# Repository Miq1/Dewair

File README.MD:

# Important note
This project now is maintained on [Codeberg.org only](https://codeberg.org/Miq19/Dewair). The code here will be frozen at the current (Mar 30, 2025) state.

## Multi-purpose environment sensor device

DewAir was originally created to measure temperatures, humidity and dew point inside and outside a room and 
control a ventilator to dry out the room. 
It has been modified in the meantime to accomodate other functions as temperature alarm, remote weather sensor etc.

For this purpose it can be equipped with none, one or two DHT22 sensors, either plugged into the device or detached by a 3-wire cable.
Control over the vent is provided by a relais connected locally or over Modbus TCP to remotely switch a socket.

The device can be configured with a built-in HTML page or over Modbus TCP.
The latter also allows for data retrieval and maintenance. 
If more than one DewAir device is used, one can retrieve the sensor data from another over Modbus TCP, thus saving sensors. 

Power is supplied by USB or 5V, sensors and relais driver are powered internally.
Power consumption is below 90mA normally.

For schematics, PCB designs and 3D printable enclosures see the "Extras" folder.

### Installation

### Usage instructions

#### Start sequence
If powered on, the device will execute some initial steps until reaching normal function.
If it never was configured before (no valid configuration data found) it will immediately start Configuration mode (see next section). 
This is indicated by a slow triple blink pattern of the status LED.

Else there is a short (3s) fast blinking period. If you will press the button within this time, Configuration mode will be entered unconditionally.

Next configuration data is read, a WiFi connection is attempted with the given SSID and password. A fastly blinking LED will signal it.
Once a connection is established, both sensors are checked. If a sensor is found reacting the respective LED will turn on.

At this point the regular state is reached.

#### Configuration mode
In Configuration mode, the device will span its own WiFi network with a name of "DewAir-xxxxxx" and the given password in the source. This by default is "Maelstrom".

You will have to connect to that network to get access to the configuration. Please note that this WiFi is unencrypted and should not be kept online for too long.

Next you will want to open a browser to call the configuration HTML page with URL ``http://192.168.4.1/``. Note again that this is without TLS, so use ``http://``, not "https"!

The configuration page has several parts, described top to bottom below. Most input fields have minimum and maximum values that you may see if hovering over it with your mouse pointer.
The configuration may be invisible in parts at the first time, necessary detail input fields will be swapped in or out depending on your settings.

The most important part is the first, where you will have to enter a name of the new device and the WiFi credentials of your local WiFi for the device to connect to.
Below that you may give an OTA password in case you are planning to update the firmware over air.

The next is the "master switch". This is used to completely switch the logic and target switching on or off. With it you may temporarily disable the device's activities for re-configuration etc. It is advisable to leave it OFF for the first time you are configuring it to be able to cross-check your configurations before going live.

Next comes the "fallback policy". This is to set a default target state in case the sensors or logic will fail at some time.
If set to ON, a failure will drive the device to unconditionally switch the target to ON.
The device logic may be resumed as soon as the causing failure is gone again.
The advisable state of the fallback switch is totally up to you and your application. A frost protector f.i. may better be switched ON, while a motorized door may have to be OFF instead.

Finally the "hysteresis" can be adjusted. Hysteresis means defining a number of necessary, consecutive measurements, whose results have lead to the same logic decision to switch the target.
Hysteresis consists of two components: a number of measurements in a row necessary and the time between measuring actions.
To give an example: a number of 5 measurements and a time of 20s will require the logic to decide the same for all 5 checks in 100s.
Only if all 5 resulted in either all ON or all OFF decisions, the switch finally will be done, if applicable.
The intended result is a less "nervous", steady switching behaviour that does not react on single dropout measurements.

The target definition is required should you want to physically switch something on or off based on the sensor data.
If the device is used as a temp/humidity sensor only, the target may be left unconfigured.
A target may be one of three variants: "ignore", if not relevant as described before, "connected", if the device's relay port is used for it, or "Modbus" for a remote "[Smartdose](https://github.com/eModbus/Smartdose)" socket addressed via Modbus.
To use the latter, the TCP IP address, Modbus port number and Modbus server ID for it are required.

Sensor configuration is quite similar to that of the target device.
The "ignore" option leaves the respective sensor slot unregarded. At the same time the combo conditions (see below) will vanish, since 
these only make sense with two sensors present.

The data for a remote, Modbus-connected sensor are the same as before for the target, with one addition: sensor slot.
A remote sensor must reside in another DewAir device to be addressed. As there are two sensor slots, you will need to name the one you are referring to.

A typical application for a remote sensor is to have just one sensor outside the building and all other devices inside it referring to the values of that one sensor.

The conditions section allows to set the conditions the respective sensor must detect to enable the target to be switched on.
Temperature, humidity or dew point can be addressed separately, the results of the evaluations are combined by a logical "and".
If you f.i. want to switch the target on a temperature higher than 10&#176;C and do not care about humidity or dew point, you will want to click on "above" in the temperature line and enter a value of 10 in the data input field. 
Both humidity and dew point options need to be set to "ignore".

Conditions set for a device that later was set to "ignore" as a device will remain unconsidered.

Likewise the combination conditions can be set. There always is a difference of the respective measurement of sensors S0 and S1 taken as the criteria for the conditions.
The settings for the conditions are identical to those with the individual sensor conditions.

#### LED decoding
There are four LEDs on the device in this order: status, S0, S1 and target. 
I recommend to use a different LED color for the status LED for better recognition.

##### Status LED
It will signal the general state the device is in. The start sequence is described above.

In manual mode the status LED will be steadily on, the target LED will show the switch state of the target.

If the target is supposed to be off as result of the evaluation of the conditions, the status LED will display a slow single blinking pattern.

Else, if the target is to be on, the status LED will send a triple blink with a pause in between.

Whenever a measurement is initiated, the status LED will turn on and off after it.

##### Sensor LEDs S0/S1
The respective sensor LED will turn on, if the sensor was configured and a measurement was successful.
A sensor not configured will be displayed by its LED being constantly off.

If a sensor was not responding, the LED will start blinking very quickly. It will resume the regular pattern as soon as the sensor responded again.

##### Target LED
For remote (Modbus) targets, the LED will behave like the sensor leds do: steady on for responding target, quick blinking when the target did not react.

A local target has no such diagnosis, but its state (on or off) will be shown by the LED being lit for ON and dark for OFF state.

#### Button functions
Besides the special interaction during startup (see above for the start sequence) the push button has three different applications.

- Quick press<br/>will start a check of the sensors and target, if any, like is done repeatedly while the device is running.
- Long press<br/>starts manual mode. In it, the sensors are ignored and further short presses will switch the target on and off in turns.
  Another long press will end manual mode and return to automatic control.
- Double click<br/>the conditions for sensor S0, S1 and the combination conditions are checked. If the respective conditions are met,
  the respective sensor LED will light. The target LED stands for the combination conditions.

### Modbus register map

| Register address | type | Contents | Write? | Remarks |
| ----------------:| ---- | -------- |:------:| ------- |
| 1       | uint   | Master switch   | YES | Disable switching logic |
| 2, 3    | float  | S0 temperature  |     | DHT22 sensor 0 |
| 4, 5    | float  | S0 humidity     |     |                |
| 6, 7    | float  | S0 dew point    |     |                |
| 8, 9    | float  | S1 temperature  |     | DHT22 sensor 1 |
| 10, 11  | float  | S1 humidity     |     |                |
| 12, 13  | float  | S1 dew point    |     |                |
| 14      | uint   | Switch state    |     |  Current target switch state |
| 15      | uint   | Restart count   |     |  Number of reboots since last init |
| 16      | uint   | Run time in minutes | |  Minutes since last reboot. Will halt at 65535. |
| 17      | uint   | S0 health       |     |  Each '1' bit stands for a successful read |
| 18      | uint   | S1 health       |     |                |
| 19      | uint   | Target health   |     |                |
| 20      | uint   | Measuring interval in seconds | YES | Must be 10 &le; n &le; 3600 |
| 21      | uint   | Hysteresis steps | YES | Must be 1 &le; n &le; 16 |
| 22      | uint   | S0 type          | YES | 0: none<br/> 1: connected locally<br/> 2: ModbusTCP source<br/> 3: reserved |
| 23, 24  | byte[4] | S0 Modbus IP address | YES | MSB first |
| 25      | uint   | S0 Modbus port number | YES | Must be &ge; 1 |
| 26      | byte[2] | MSB: S0 Modbus server ID<br/>LSB: slot number | YES | 1 &le; MSB &le; 247<br/> LSB: 0 or 1 |
| 27      | special | S0 temperature condition:<br/> bits 14,15: condition type<br/> bits 0..13: compare value | YES | *type:*<br/> 0: disregard<br/> 1: less than value<br/> 2: greater than value<br/>3: reserved<br/>*value:*<br/> ``float val = (int(value) - 2048) / 10.0;``|
| 28      | special | S0 humidity condition/value (as above) | YES | see above |
| 29      | special | S0 dew point condition/value (as above) | YES | see above |
| 30      | uint   | S1 type          | YES | see S0 type |
| 31, 32  | byte[4] | S1 Modbus IP address | YES | MSB first |
| 33      | uint   | S1 Modbus port number | YES | Must be &ge; 1 |
| 34      | byte[2] | MSB: S1 Modbus server ID<br/>LSB: slot number | YES | 1 &le; MSB &le; 247<br/> LSB: 0 or 1 |
| 35      | special | S1 temperature condition:<br/> see S0 | YES | see S0 |
| 36      | special | S1 humidity condition/value (as above) | YES | see above |
| 37      | special | S1 dew point condition/value (as above) | YES | see above |
| 38      | uint   | Target type           | YES | 0: none<br/> 1: connected locally<br/> 2: Modbus TCP target<br/> 3: reserved |
| 39, 40  | byte[4] | Target Modbus IP address | YES | MSB first |
| 41      | uint   | Target Modbus port number | YES | Must be &ge; 1 |
| 42      | uint   | Target Modbus server ID   | YES | **MSB only!**<br/> Must be 1 &le; SID &le; 247 |
| 43      | special | (S0 temperature - S1 temperature) condition type and value | YES | see S0 temperature condition and type above |
| 44      | special | (S0 humidity - S1 humidity) condition type and value | YES | see above |
| 45      | special | (S0 dew point - S1 dew point) condition type and value | YES | see above |
| 46      | uint    | nibble 0: number of combo conditions met<br/>nibble 1: number of S1 conditions met<br/>nibble 2: number of S0 conditions met<br/>nibble 3: unused |     | debug info |
| 47      | uint    | Fallback switch setting | YES | 0: OFF<br/>else: ON |
| 48      | uint    | Number of history slots |     | 1440 minutes a day / slots = minutes within a slot for values to be averaged |
| 49      | uint    | Start address of first history slot entry |     | see section below! |
| 50      | uint    | Currently written history data slot |     | see below! |
| 51 .. 63 |    | *reserved* | YES | future extension space |
| 64      | uint    | Number of event slots |    | if 0: no events available |
| 65 ..   | special | Logged events (number see register 64) |     | bits 11 .. 15: Event code<br/>bits 6 .. 10: day/hour<br/>bits 0 .. 5: month/minute |

#### History entries
For each history slot, temperatures and humidities of both sensors (if available) are averaged over the values within that slot.
The slots are ordered from 0=00:00 to (history slots - 1)=last before midnight.
Times as are related to slots can be calculated as follows:
- 1440 / history slots = minutes per slot. The default 120 slots translate to 12 minutes per slot.
- A given slot number needs to be multiplied by the minutes per slot, then has to be separated into hour and minute.
  Example: slot 67 is 67 * 12 = 804 minutes since midnight. Divided by 60 this is 13 hours. The remainder are 24 minutes.
  Hence the slot 67 is starting at 13:24 (1:24pm).
To fit into an ``uint16_t`` register, values are encoded:
- temperature: (avg(temp) + 100) * 10. ``1256`` will mean 25.6 degrees.
- humidity: avg(hum) * 10. ``489`` stands for 48.9% RH.
Additionally the percentage of the target being on is collected.
All time ON withing the slot is 100%, never ON is 0%.

| Register address | type | Contents | Write? | Remarks |
| ----------------:| ---- | -------- |:------:| ------- |
| History offset..history offset + history slots - 1 | uint   | Sensor 0 temperature history values |  | encoded as described above |
| like the above, History slots added | uint   | Sensor 0 humidity history values |  | encoded as described above |
| like line 1, 2 * History slots added | uint   | Sensor 1 temperature history values |  | encoded as described above |
| like line 1, 3 * History slots added | uint   | Sensor 1 humidity history values |  | encoded as described above |
| like line 1, 4 * History slots added | uint   | Target switch ON percentage |  | see section above |

### Applications

#### Dew point ventilation

#### Frost protection

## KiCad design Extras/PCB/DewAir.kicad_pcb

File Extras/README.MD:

# Extras
This folder contains additional components and materials I developed for my DewAir devices - namely, the dew point ventilation controller and the frost protection device.

- Enclosure contains FreeCAD 3D designs and STL files for a small and a large box. The small one is powered by USB or 5V and needs a WiFi socket as target device, the larger box has all inside to run autonomously when connected to a wall power outlet.
- Fan Mount has 3D FreeCAD designs and STLs as well for attaching a 100mm standard tube ventilator or a 100mm air gauge to a window pane. I replaced the glass panes by acrylic glass and cut a hole in in to fit the mount. A drilling/cutting template can be 3D printed as well.
- PCB holds all KiCAD and Gerber files necessary to have the PCB manufactured.
- ``DewAir.cpp`` is a Linux command line tool to configure and control any DewAir device. It requires the Linux port of the [eModbus](https://github.com/eModbus/eModbus) library to be built - found there in the [examples/Linux](https://github.com/eModbus/eModbus/tree/master/examples/Linux) directory.
See below for build instructions etc.

### DewAir Linux tool
All interaction with the device is done by Modbus TCP. 
You of course may use other Modbus TCP clients to achieve the same, but you will need to closely inspect the Modbus register list for it.
The ``DewAir`` tool has all the definitions built in and lets you use plain text words to interact with the device.

#### Build and Install
As a prerequisite you will need to build the Linux eModbus library as mentioned in the first section.
With that available you can compile the program by
```
g++ DewAir.cpp -Wextra -DLOG_LEVEL=3 -MMD -leModbus -pthread -lexplain -o DewAir
```
#### Usage
Running ``DewAir`` without any parameter will display the supported options:
```
micha@LinuxBox:~$ DewAir 
At least one argument needed!

Usage: DewAir host[:port[:serverID]]] [cmd [cmd_parms]]
  cmd: INFO | ON | OFF | EVERY | EVENTS | INTERVAL | HYSTERESIS | TARGET | SENSOR | CONDITION | FALLBACK | REBOOT | ERRORS | HISTORY
  ON|OFF
  FALLBACK ON|OFF
  EVERY <seconds>
  EVENTS
  ERRORS
  HISTORY
  INTERVAL <seconds>
  HYSTERESIS <steps>
  TARGET NONE|LOCAL|<host[:port[:serverID]]]>
  SENSOR <0|1> NONE|LOCAL|<<host[:port[:serverID]]]> <0|1>>
  CONDITION <SENSOR <0|1>>|DIFF TEMP|HUM|DEW IGNORE|<BELOW|ABOVE <value>>
  REBOOT
```
``DewAir`` needs a device as first parameter in any case.
This can be the DNS name the device has been assigned, or a detailed address consisting of an IP address, a port number and a Modbus server ID, separated by colons (':').
If omitted, the server ID defaults to 1, the port number is 502 by default.

After the address of the device a command is expected. If none was given, ``INFO`` is taken as a default.

#### INFO
With ``INFO`` the current data is requested from the device. Sample output:
```
micha@LinuxBox:~$ DewAir anbau 
Using 192.168.178.30:502:1
Master switch ON
Fallback: switch ON
Sensor 0:  12.1°C   56.0%    3.6°C  - FFFF
Sensor 1:   6.4°C   45.8%   -4.4°C  - FFFF
Target is OFF - FFFF 192.168.178.40:502:1
Measuring every 30 seconds, hysteresis steps: 4
86 restarts, run time since last restart 24:48
40 event slots
120 history slots starting at 400, current is 83
Switch conditions (all must be true): 
 + S0 temperature below   5.0°C
Condition state: 0233
```
You see how the DNS name ``anbau`` is translated internally to a full address.
The device is active (master is ON), on failures it will switch the target to ON.
Both sensors are connected locally and are performing well (``FFFF`` tells us the last 16 sensor requests were successful).
The target device is a Modbus-controlled remote socket, it is currently OFF and communication was okay (``FFFF`` again).
Sensors are requested every 30 seconds and 4 consecutive identical evaluations of the conditions set will trigger a switching action.
The device was restarted 86 times and is running more than a day now after the last restart.
It does register the last 40 events (see below) and the data history has 120 time slices over a day. Modbus register 400 holds the first history value.
The device is set to switch the target as soon as sensor 0 will report a temperature below 5 degrees. Current temperature is above that, so the state is not ``0333`` as it would be with all conditions met.

#### ON/OFF
This will activate or deactivate the device. The 'Master switch' is turned ON or OFF.
If set to OFF, the device will work as normal, but never will touch the target's state.

#### FALLBACK
If sensors have malfunctions or are not responding, there is no reliable evaluation of the switch conditions possible any more.
``FALLBACK`` defines the target state that will be set in such situations.
F.i. a frost protection device may set to fall back to ON state to prevent freezing - for the cost of unnecessary energy wasted.

#### EVERY
``EVERY`` will request and print out the sensor and target state values in the intervals given as additional seconds parameter.
Note that this value must be 60 or higher to prevent the device being flooded with requests.
The output is a comma separated list for easy processing in a spreadsheet program. To have an output readable on the terminal you should pipe it through a ``tr`` like in
```
micha@LinuxBox:~$ DewAir anbau every 60 | tr ';' '\t'
Using 192.168.178.30:502:1
Time    S0                      S1                      Diff                    target
        temp    hum     dew     temp    hum     dew     temp    hum     dew
17:25   12.2    53.0    2.9     5.6     47.2    -4.8    6.6     5.8     7.7     0
```
Output can be stopped by ``Ctrl C`` only.

#### EVENTS
Important things happening will be recorded on the device in the ``EVENTS`` list. It looks like
```
micha@LinuxBox:~$ DewAir anbau events
Using 192.168.178.30:502:1
40 event slots found.
target off           18:06
target off           20:05
target off           20:06
target off           22:05
target off           22:06
date change     01.03.
target off           00:05
target off           00:06
target off           01:09
target off           02:05
target off           04:05
target on            04:49
target off           04:54
target on            05:28
...
```
(Note: in this example the target itself is programmed to turn on every two hours, so as soon as the DewAir device notices the target being ON, it will switch it OFF again).

#### ERRORS
Similar to the events, Modbus errors are recorded on the device.
With the ``ERRORS`` command you may retrieve what was stored:
```
micha@LinuxBox:~$ DewAir anbau errors
Using 192.168.178.30:502:1
Back : ERR  Count
    0:  00    229 - Success
    1:  E0      1 - Timeout
    2:  00    410 - Success
    3:  EA      1 - IP connection failed
    4:  00    937 - Success
```
Only if the Modbus state has changed a new entry is made. Else only the number of occurrences of the same state will be counted.
Note that the most recent state is shown on top, the lower, the older the stes are.

#### HISTORY
All sensor data and target states are collected for 24h. Values older will be replaced by current values as time proceeds.
The data is averaged over time slots. A slot is 12 minutes wide in the default code.
Hence you will have 120 slots per 24h that can be retrieved in a single Modbus request.
There are 120 such values for sensor 0 temperature, humidity, sensor 1 temperature and humidity and the target state value. 
A complete history data set will have 600 values, each in a Modbus register.
Floating point sensor values are encoded to fit into the 16 bits of a Modbus register.
The coding scheme is described on the main page - see section 'History' there.

The ``HISTORY`` command will do all 5 requests and the decoding in one step and outputs the data as a comma-separated list to be processed in a spreadsheet program.
It is advisable to catch the output in a file and open it in a spreadsheet:
```
micha@LinuxBox:~$ DewAir anbau history > anbau.csv
```
With a bit of massaging in the spreadsheet you can quickly get some nice diagrams:

A sixth column is added to the output that is almost empty. The exception is a ``#`` sign in that row where the next slot will be written.
So right of that line is data from the previous day, left of it the data for the current day up to now.

In the diagram above I used a simple formula (``=IF($H3=" ";$G2;100)``) to have a line jump up at the current slot. It will take a zero as start value and always replicate the value of the line above - except if the neighbouring cell has something other than a blank in it; then the value will set to 100.

#### REBOOT
A mechanism has been integrated to remotely restart a DewAir device. 
It makes use of the user-definable Modbus function code 0x44.
``REBOOT`` has to be sent twice within 60 seconds to have an effect. 
This is meant as a basic security mechanism. 
The first ``REBOOT`` will be answered by ``armed.``, the second, if received within the 60s period, will print out ``rebooting.``.
If the second commend is late or not given at all, the ``armed`` state will be reset on the device.

#### INTERVAL ``<seconds>`` and HYSTERESIS ``<turns>``
These two commands will modify the reaction speed of the device on changing sensor data.
Data is sampled every ``INTERVAL`` seconds. Note that the seconds parameter can not be lower than 20 to not overload the device.

``HYSTERESIS`` sets a number of sampling periods where the sampled values are fulfilling the switching conditions without exception.
If that happens, a switch is executed.

F.i. a combination of 30 seconds and a hysteresis of 6 will require the switch conditions to last at least 3 minutes to trigger a switch.
Higher values will lead to a slower, smoother switching behaviour, whereas short intervals or less hysteresis periods will let the device react more quickly.
It depends from your application which may be the adequate setting.

#### TARGET
The ``TARGET`` command lets you define if there is a switching target at all and what type it is.

A ``TARGET NONE`` will disable any switching actions, while sensor data still is collected.
This may be useful if you are using a DewAir device as a remote temperature/humidity platform to read these data and make it available to other devices.
Please see the ``SENSOR`` explanations in the section below.

``TARGET LOCAL`` enables the device to use the internal relay/SSR logic as a target. 
A stand-alone DewAir device may switch a built-in socket this way.

Finally ``TARGET <Modbus address>`` allows for remote target devices that can be switched by a Modbus request.
At this time only the [Smartdose](https://github.com/eModbus/Smartdose) type of devices is supported. 
Other WiFi sockets will need a different command or even different protocol that would have to be integrated first.
Contributions are always welcome... :wink:

The Modbus address needs to be given as described above for the first parameter of the DewAir application itself: either a DNS name or a set of IP address, port and server ID, joined by colons ':'.

#### SENSOR
Each of the two attachable sensors may be non-existent, plugged in locally into the device or other DewAir devices in the same local network.

``SENSOR`` always needs a sensor number first, that can be ``0`` for the first or ``1`` for the second DHT22 sensor.

After that we can have ``NONE`` to disable the sensor slot, ``LOCAL`` for sensors connected by wire to the device, or a Modbus address again to connect to another DewAir device.

The Modbus address has to follow the very same rules as described above for the DewAir application or the ``TARGET`` parameter.
It requires one more parameter after it, though: the sensor slot on the remote device.
This slot addresses the two sensors on that device the same way as we are doing here: ``0`` is the first, ``1`` the second sensor.

Instead of collecting the data locally, a remote sensor will be requested by Modbus. 
Note that due to the communication delays and collecting interval on the remote device the data gathered remotely may not exactly be measured at the same time the request was sent, but will be delayed for some seconds.

#### CONDITION
If and when a target gets switched is depending from the conditions you have defined in regards to the sensor data.
The ``CONDITION`` command lets you set these conditions at will.

First you will have to tell what conditions you are going to set:
- ``SENSOR 0`` or ``SENSOR 1`` will select the respective sensor
- ``DIFF`` instead will target on conditions for both sensors combined. Note that this is not possible if one or both sensors are set to ``NONE``!

The next parameter selects the data type you are using for the condition - ``TEMP`` for temperature, ``HUM`` for humidity or ``DEW`` for the dew point temperature evaluated internally.

Last is the condition proper:
- ``IGNORE`` disables it to not be regarded any more
- ``BELOW <value>`` will result ``TRUE`` if the selected data is lower than the given ``<value>``
- opposite, ``ABOVE <value>`` will be ``TRUE`` if the data is higher than ``<value>``

Example:
```
DewAir condition sensor 0 temp below 5
```
will require the first sensor's temperature to be lower than 5 degrees Celsius to be evaluated to ``TRUE``.

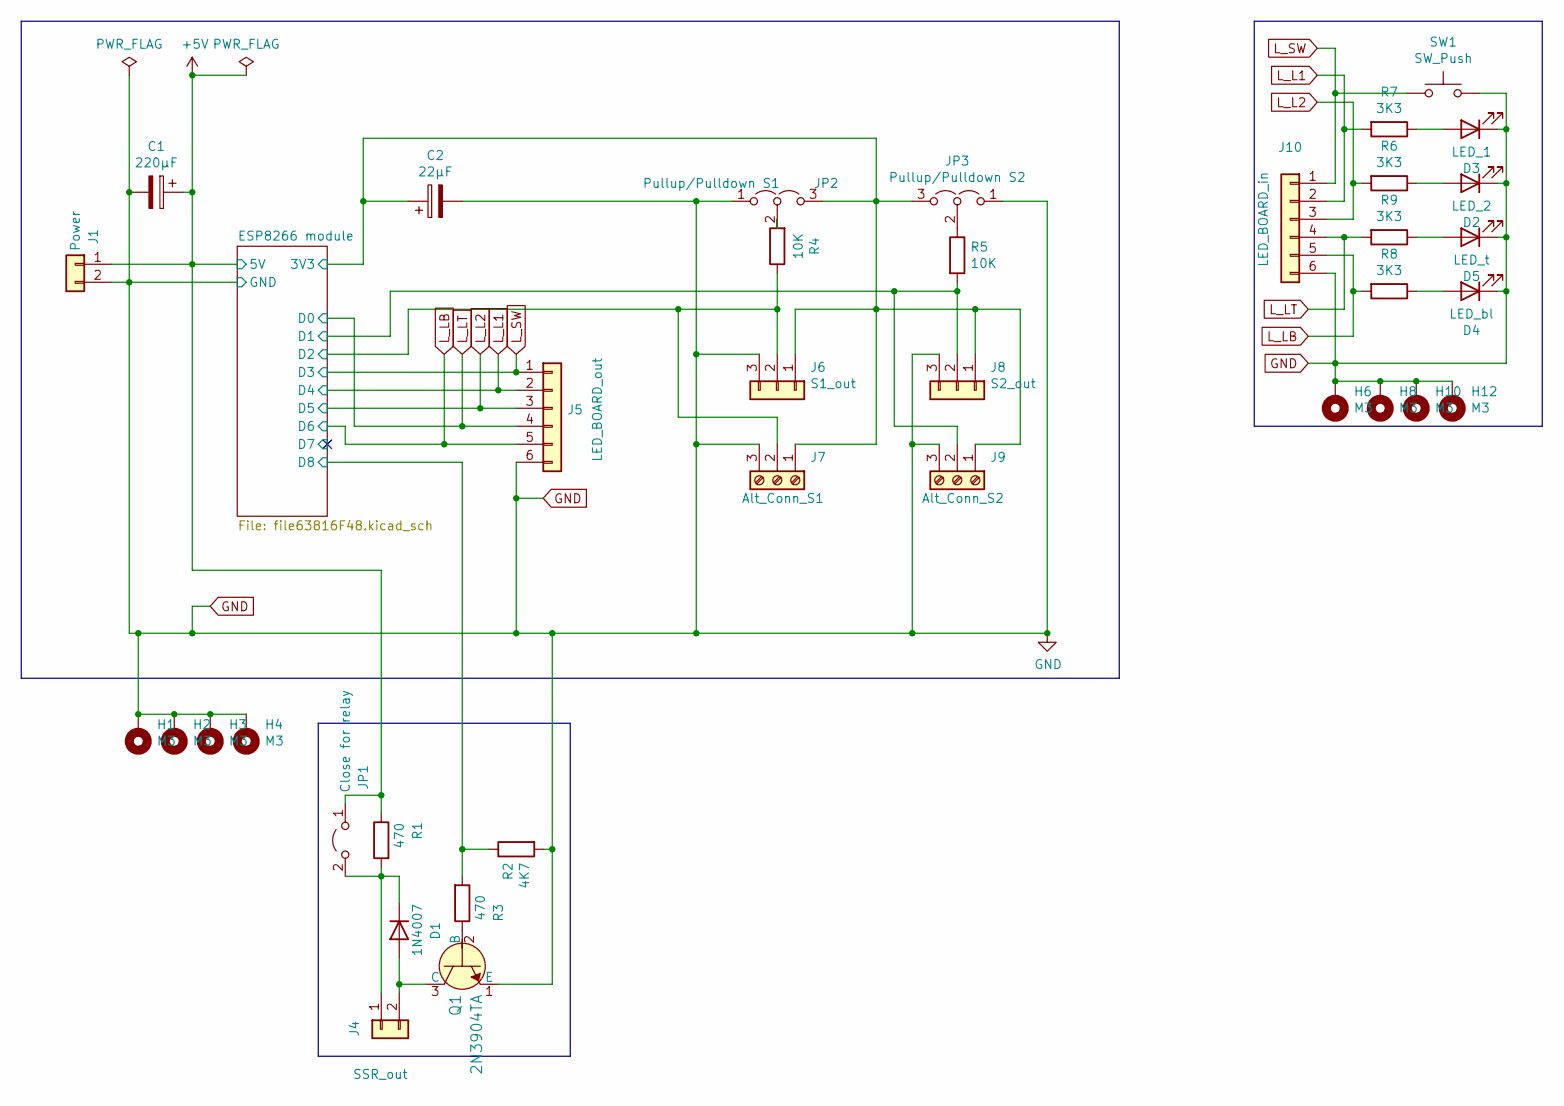
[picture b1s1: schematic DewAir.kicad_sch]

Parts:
C1: 220µF; CP_Radial_D5.0mm_P2.00mm
C2: 22µF; CP_Radial_D4.0mm_P2.00mm
D1: 1N4007; D_A-405_P7.62mm_Horizontal
D2: LED_2; LED_D3.0mm
D3: LED_1; LED_D3.0mm
D4: LED_bl; LED_D3.0mm
D5: LED_t; LED_D3.0mm
H1, H2, H3, H4, H6, H8, H10, H12: M3; MountingHole_3.2mm_M3_DIN965_Pad
J1: Power; TerminalBlock_bornier-2_P5.08mm
J4: SSR_out; TerminalBlock_bornier-2_P5.08mm
J5: LED_BOARD_out; Pin_Header_Straight_1x06_Pitch2.54mm
J6: S1_out; JST_XH_B03B-XH-A_03x2.50mm_Straight
J7: Alt_Conn_S1; TerminalBlock_bornier-3_P5.08mm
J8: S2_out; JST_XH_B03B-XH-A_03x2.50mm_Straight
J9: Alt_Conn_S2; TerminalBlock_bornier-3_P5.08mm
J10: LED_BOARD_in; Pin_Header_Straight_1x06_Pitch2.54mm
JP1: Close for relay; Pin_Header_Straight_1x02_Pitch2.54mm
JP2: Pullup/Pulldown S1; Pin_Header_Straight_1x03_Pitch2.54mm
JP3: Pullup/Pulldown S2; Pin_Header_Straight_1x03_Pitch2.54mm
Q1: 2N3904TA; TO-92_Inline; MPN 2N3904TA; Digi-Key_PN 2N3904TAFSCT-ND
R1, R3: 470; R_Axial_DIN0207_L6.3mm_D2.5mm_P7.62mm_Horizontal
R2: 4K7; R_Axial_DIN0207_L6.3mm_D2.5mm_P7.62mm_Horizontal
R4, R5: 10K; R_Axial_DIN0207_L6.3mm_D2.5mm_P7.62mm_Horizontal
R6, R7, R8, R9: 3K3; R_Axial_DIN0207_L6.3mm_D2.5mm_P7.62mm_Horizontal
SW1: SW_Push; SW_PUSH_6mm_h9.5mm

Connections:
+5V: C1.1, J1.1, JP1.1 (A), R1.1; also elsewhere on the board
/ESP8266 module/3V3: C2.1, J6.1, J7.1, J8.1, J9.1, JP2.3 (B), JP3.3 (B); also elsewhere on the board
/ESP8266 module/D1: J8.2, J9.2, R5.2; also elsewhere on the board
/ESP8266 module/D2: J6.2, J7.2, R4.1; also elsewhere on the board
/ESP8266 module/D8: R2.1, R3.2; also elsewhere on the board
GND: C1.2, C2.2, D2.1 (K), D3.1 (K), D4.1 (K), D5.1 (K), H1.1, H2.1, H3.1, H4.1, H6.1, H8.1, H10.1, H12.1, J1.2, J5.6, J6.3, J7.3, J8.3, J9.3, J10.6, JP2.1 (A), JP3.1 (A), Q1.1 (E), R2.2, SW1.2; also elsewhere on the board
L_L1: J5.2, J10.2, R7.2; also elsewhere on the board
L_L2: J5.3, J10.3, R6.2; also elsewhere on the board
L_LB: J5.5, J10.5, R8.2; also elsewhere on the board
L_LT: J5.4, J10.4, R9.2; also elsewhere on the board
L_SW: J5.1, J10.1, SW1.1; also elsewhere on the board
unnamed: D1.1 (K), J4.1, JP1.2 (B), R1.2
unnamed: D1.2 (A), J4.2, Q1.3 (C)
unnamed: D2.2 (A), R6.1
unnamed: D3.2 (A), R7.1
unnamed: D4.2 (A), R8.1
unnamed: D5.2 (A), R9.1
unnamed: JP2.2 (C), R4.2
unnamed: JP3.2 (C), R5.1
unnamed: Q1.2 (B), R3.1

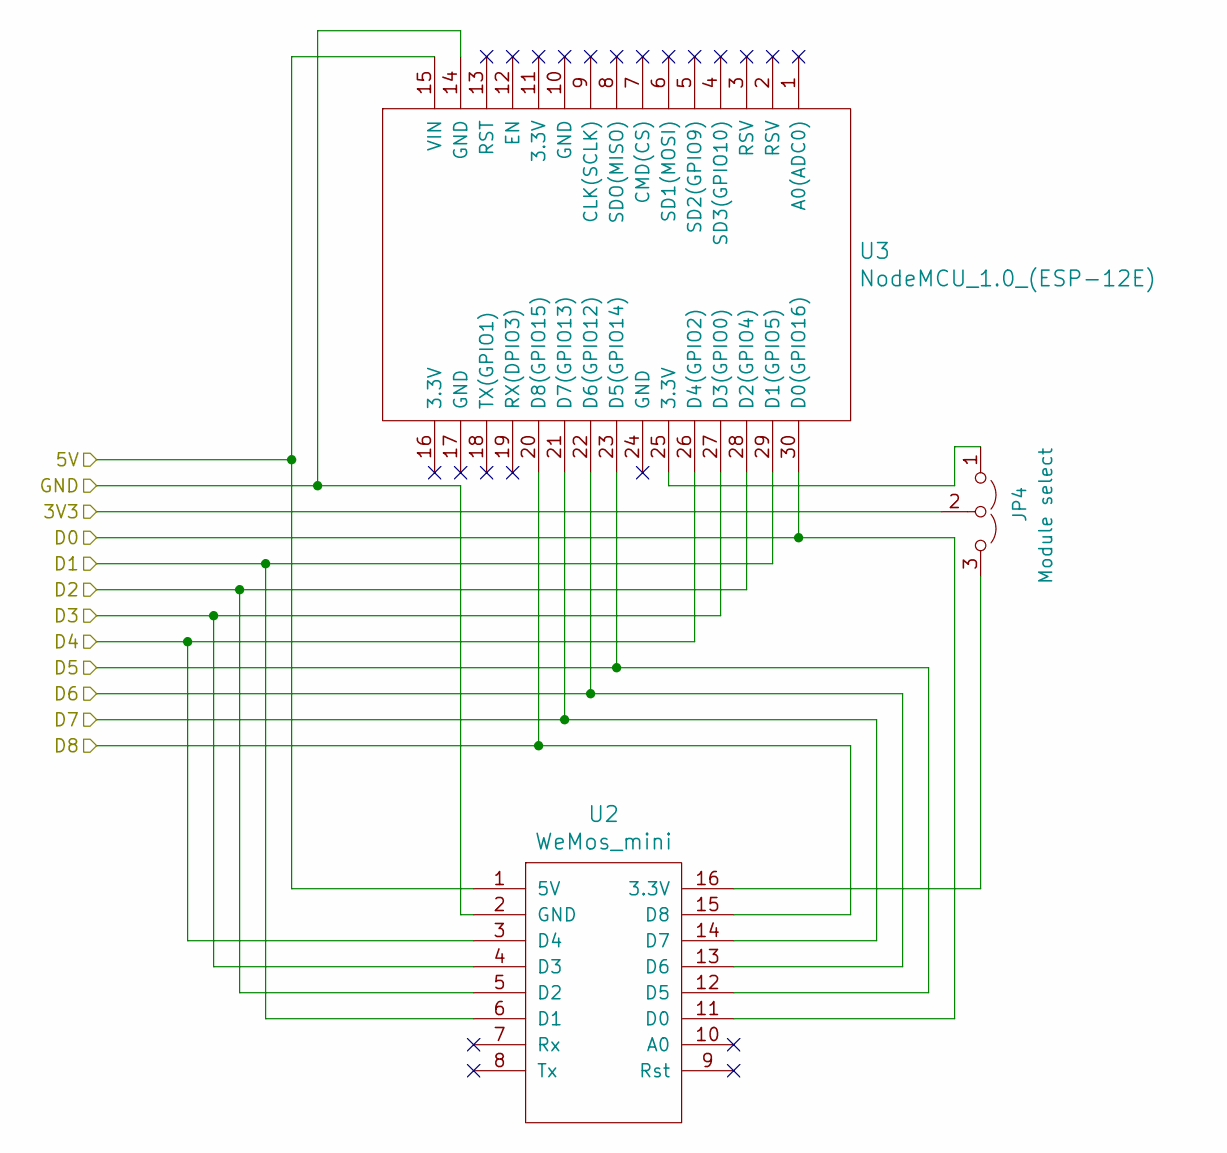
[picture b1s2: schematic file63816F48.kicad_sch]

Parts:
JP4: Module select; Pin_Header_Straight_1x03_Pitch2.54mm
U2: WeMos_mini; D1_mini_board
U3: NodeMCU_1.0_(ESP-12E); NodeMCU Amica

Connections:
+5V: U2.1 (5V), U3.15 (VIN); also elsewhere on the board
/ESP8266 module/3V3: JP4.2 (C); also elsewhere on the board
/ESP8266 module/D1: U2.6 (D1), U3.29 (D1(GPIO5)); also elsewhere on the board
/ESP8266 module/D2: U2.5 (D2), U3.28 (D2(GPIO4)); also elsewhere on the board
/ESP8266 module/D7: U2.14 (D7), U3.21 (D7(GPIO13))
/ESP8266 module/D8: U2.15 (D8), U3.20 (D8(GPIO15)); also elsewhere on the board
GND: U2.2 (GND), U3.14 (GND); also elsewhere on the board
L_L1: U2.3 (D4), U3.26 (D4(GPIO2)); also elsewhere on the board
L_L2: U2.12 (D5), U3.23 (D5(GPIO14)); also elsewhere on the board
L_LB: U2.13 (D6), U3.22 (D6(GPIO12)); also elsewhere on the board
L_LT: U2.11 (D0), U3.30 (D0(GPIO16)); also elsewhere on the board
L_SW: U2.4 (D3), U3.27 (D3(GPIO0)); also elsewhere on the board
unnamed: JP4.1 (A), U3.25 (3.3V)
unnamed: JP4.3 (B), U2.16 (3.3V)

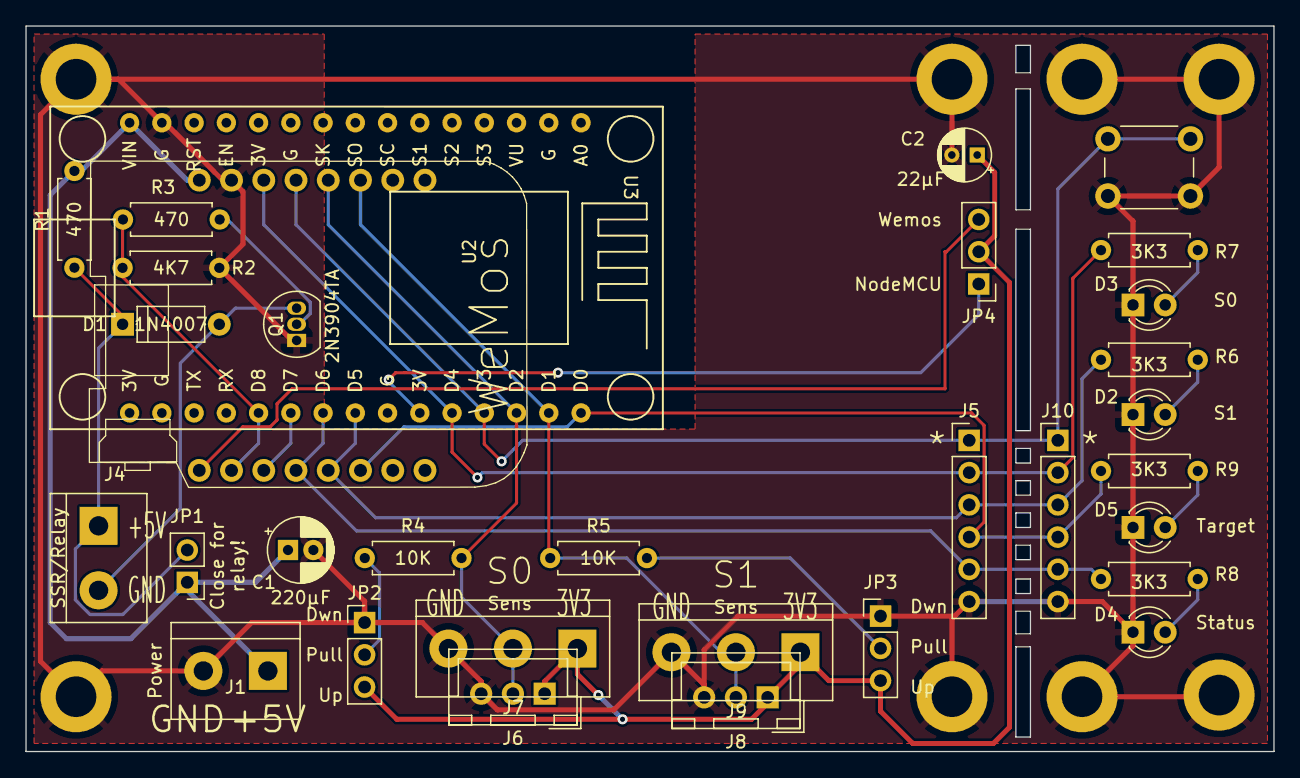
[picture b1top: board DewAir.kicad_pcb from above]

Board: 2 copper layers, 98.3 x 57.1 mm, 40 parts (0 on the bottom side), 23 nets.

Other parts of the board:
H11: M3; MountingHole_3.2mm_M3_DIN965_Pad

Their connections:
GND: H11.1; also elsewhere on the board

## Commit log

2022-10-16 Initial version
2022-10-16 Adjust .gitignore
2022-10-16 Update version info
2022-10-18 Update web interface
2022-10-19 Complete device info page
2022-10-20 Add Modbus FC 03. Correct time zone.
2022-10-21 Add Modbus write functions. A few clean-ups.
2022-10-22 Fix relay pin, start documentation
2022-10-26 Fix wrong comparison values
2022-10-28 Fix runTime overflow.
2022-11-13 Test fix-async branch
2022-11-16 Fix some compiler warnings
2022-12-14 Fix conditions evaluation w/ missing sensors
2022-12-17 Fix LED assign and irrelevant sensor treatment
2022-12-18 Add fallback switch option
2022-12-18 Add Fallback Modbus register docs
2022-12-18 Fix README layout
2022-12-18 Move README to root
2022-12-19 Work packet README
2022-12-19 Fix graphics paths
2022-12-20 Fix logic for sensors connected, but irrelevant
2022-12-20 Add to README.MD
2022-12-25 Move restarts count out of settings file
2022-12-30 Add case files
2022-12-30 Typo
2022-12-30 Add parts
2022-12-30 Initial description
2022-12-30 Add German name of CAD file
2022-12-31 Add lid variants, Sensor housing and PCB files
2023-01-01 Different sensor housing
2023-01-01 Make screw holes configurable
2023-01-05 Prevent fallback for irrelevant sensor failures
2023-01-05 Fix minor things with enclosures
2023-01-05 Fix FreeCAD error message
2023-01-06 Local target LED to reflect switch state
2023-01-06 Add more explanations
2023-01-06 Add more configuration descriptions.
2023-01-06 Fix typo
2023-01-07 Improve debug output
2023-01-13 Add fan window mount construction
2023-01-13 Change MB response handling to data/error
2023-01-13 Add basic Modbus error log for target
2023-01-24 Another rework of conditions logic
2023-01-24 Initial commit of Linux tool
2023-01-24 Add large enclosure
2023-01-26 Add updated large enclosure
2023-01-26 Amend README
2023-01-27 Crank up version to 1.0
2023-01-27 Fix minor stuff, add ventilation openings
2023-02-01 Remove use of sync HTTP in RUN mode
2023-02-02 Improve error tracking
2023-02-05 Better Modbus sensor tracking
2023-02-18 Update 3D print parts and pictures
2023-02-27 Add 24h history data
2023-02-28 Fix temperature encoding
2023-02-28 Update Modbus register docs
2023-02-28 Fix typo (sensor 1 history)
2023-02-28 Add current slot to Modbus registers
2023-02-28 Add HISTORY command to Linux app
2023-03-01 Init DewAir.cpp documentation
2023-03-01 Add diagram
2023-03-02 Add slot marker to diagram
2023-03-02 Complete Linux app docs
